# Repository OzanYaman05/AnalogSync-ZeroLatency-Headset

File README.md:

# 🎧 AnalogSync: Open-Source Zero-Latency Wireless Headset

Welcome to the **AnalogSync** project! This is a 100% open-source, DIY wireless headset system built from scratch. Unlike standard Bluetooth headphones that suffer from digital compression and audio latency, this project uses **pure analog FM transmission** to achieve **true zero-latency** and **Hi-Fi Stereo** sound. 

Whether you are a gamer, musician, or hardware enthusiast, you can buy the parts, 3D print the shell, and build your own latency-free wireless audio system!

## ✨ Key Features
* **Zero Latency (0ms):** End-to-end analog signal processing. Perfect for gaming and lip-syncing.
* **Bare-Metal I2C Control:** Custom firmware bypassing standard libraries to directly control IC registers (RDA5807M & KT0803L) for advanced stereo and bass management.
* **Optimized Power Management:** Engineered impedance matching for the TDA1308 Class-AB amplifier driving 8-Ohm speakers.
* **100% 3D Printable:** Custom-designed ergonomic headset shell and headband.

---

## 🛠️ Bill of Materials (BOM) - What You Need
Anyone can build this! Here is the complete list of parts:

**Receiver (The Headset):**
* 1x ATtiny85 Microcontroller (Overclocked to 8MHz internal)
* 1x RDA5807M FM Stereo Receiver Module
* 1x TDA1308 Class-AB Headphone Amplifier
* 2x 32mm 8-Ohm Speakers
* 2x 3.7V Li-Po Batteries & Charging Module (e.g., TP4056) **OR** 4x AA Batteries
* Assorted Capacitors & Resistors (See Schematics)

**Transmitter (The Base Station):**
* 1x Arduino (Nano or Uno)
* 1x KT0803L FM Transmitter Module *(Note: Almost any standard FM transmitter module can work!)*
* 2x Push Buttons (For frequency tuning)
* Audio Jack / Aux Cable

---

## 🚀 How to Build It (DIY Guide)

### Step 1: 3D Print or Remix the Enclosure
Navigate to the `/Mechanical` folder. As a true open-source hardware project, we currently provide the raw **Fusion 360 (`.f3d`) source files**. You can modify the parametric design to fit your head perfectly, and export the `.STL` files directly from your software to print using PLA or PETG (20% infill is recommended). *(Pre-sliced .STL files will be added in the future!)*

### Step 2: The Hardware & Solder
Check the `/Hardware` folder for the wiring diagram. 
* **Note on Amplifier:** Ensure you add a 680uF decoupling capacitor at the output of the TDA1308 to protect the 8-Ohm speakers and prevent voltage drops!

### Step 3: Flash the Firmware
Navigate to the `/Firmware` folder.
* **RX (Headset):** Flash the ATtiny85. *Make sure to burn the bootloader to 8MHz internal clock first!*
* **TX (Base):** Upload the Arduino sketch. The buttons on Pin 2 and Pin 3 allow you to scan frequencies (Default lock: 82.0 MHz).

### Step 4: Assemble & Enjoy
Put the electronics inside your fresh 3D prints, power up the transmitter with an audio source, and enjoy your zero-latency analog sound!

---

## 🤝 Contributing
Feel free to fork this project, submit pull requests, or open an issue if you have ideas to improve the audio quality or 3D design. Let's make open-source hardware better together!

## 📝 License
This project is licensed under the MIT License - see the [LICENSE](LICENSE) file for details.

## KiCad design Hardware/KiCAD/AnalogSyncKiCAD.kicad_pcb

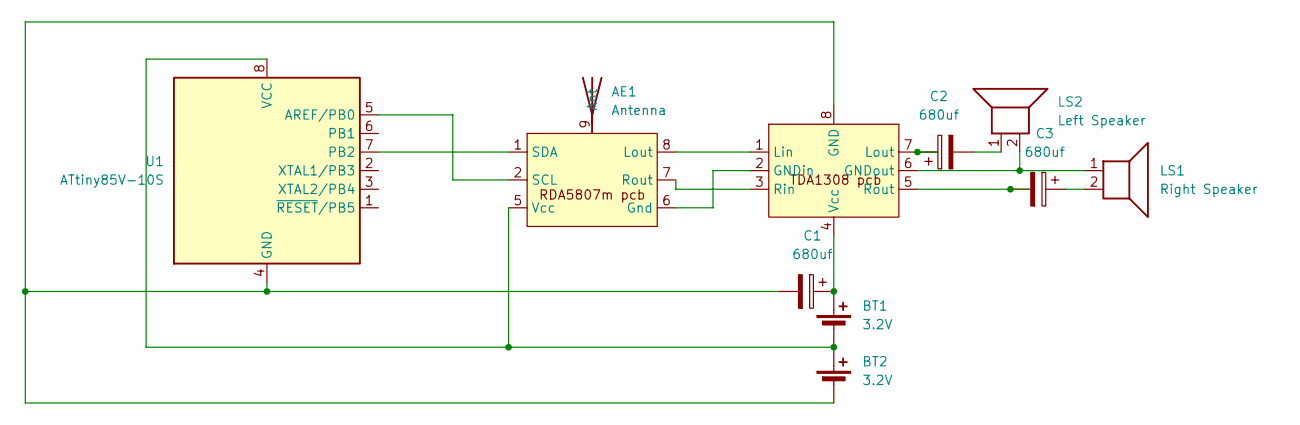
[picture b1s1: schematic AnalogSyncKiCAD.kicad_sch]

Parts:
AE1: Antenna; PinHeader_1x01_P2.54mm_Vertical
BT1, BT2: 3.2V; PinHeader_1x02_P2.54mm_Vertical
C1, C2, C3: 680uf; CP_Radial_D6.3mm_P2.50mm
LS1: Right Speaker; PinHeader_1x02_P2.54mm_Vertical
LS2: Left Speaker; PinHeader_1x02_P2.54mm_Vertical
RDA5807m1: RDA5807m pcb
TDA1308pcb2: tda1305 pcb
U1: ATtiny85V-10S; DIP-8_W10.16mm

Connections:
unnamed: AE1.1 (A), RDA5807m1.9 (Ant)
unnamed: BT1.1 (+), C1.1, TDA1308pcb2.4 (Vcc)
unnamed: BT1.2 (-), BT2.1 (+), RDA5807m1.5 (Vcc), U1.8 (VCC)
unnamed: BT2.2 (-), C1.2, TDA1308pcb2.8 (GND), U1.4 (GND)
unnamed: C2.2, LS2.1
unnamed: C3.1, LS1.2
unnamed: RDA5807m1.7 (Rout), TDA1308pcb2.3 (Rin)
unnamed: RDA5807m1.6 (Gnd), TDA1308pcb2.2 (GNDin)
unnamed: RDA5807m1.2 (SCL), U1.5 (AREF/PB0)
unnamed: RDA5807m1.1 (SDA), U1.7 (PB2)
unnamed: RDA5807m1.8 (Lout), TDA1308pcb2.1 (Lin)
unnamed: LS1.1, LS2.2, TDA1308pcb2.6 (GNDout)
unnamed: C2.1, TDA1308pcb2.7 (Lout)
unnamed: C3.2, TDA1308pcb2.5 (Rout)

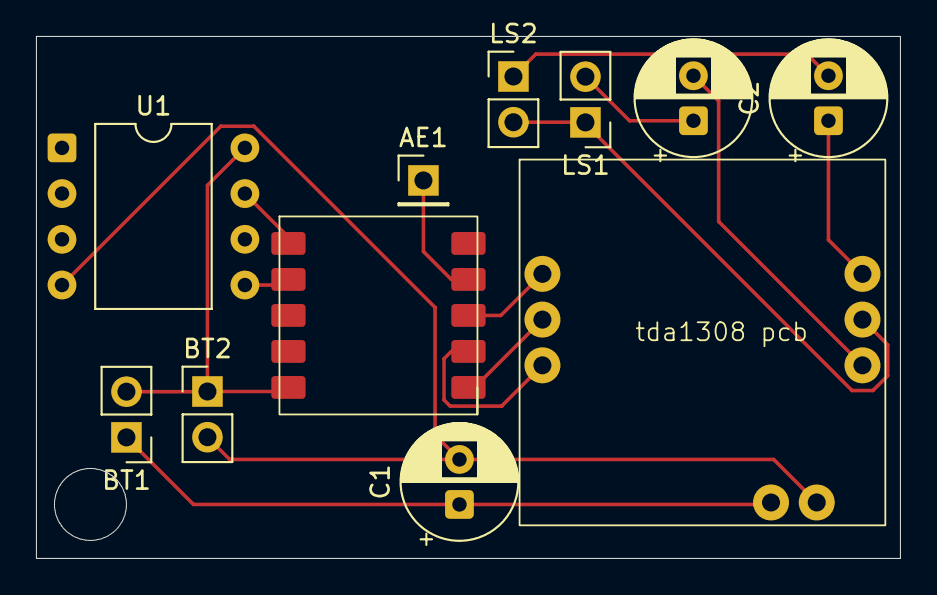
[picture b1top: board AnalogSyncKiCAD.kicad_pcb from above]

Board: 2 copper layers, 48.0 x 29.0 mm, 11 parts (0 on the bottom side), 14 nets.

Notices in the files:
README.md:
License: MIT
